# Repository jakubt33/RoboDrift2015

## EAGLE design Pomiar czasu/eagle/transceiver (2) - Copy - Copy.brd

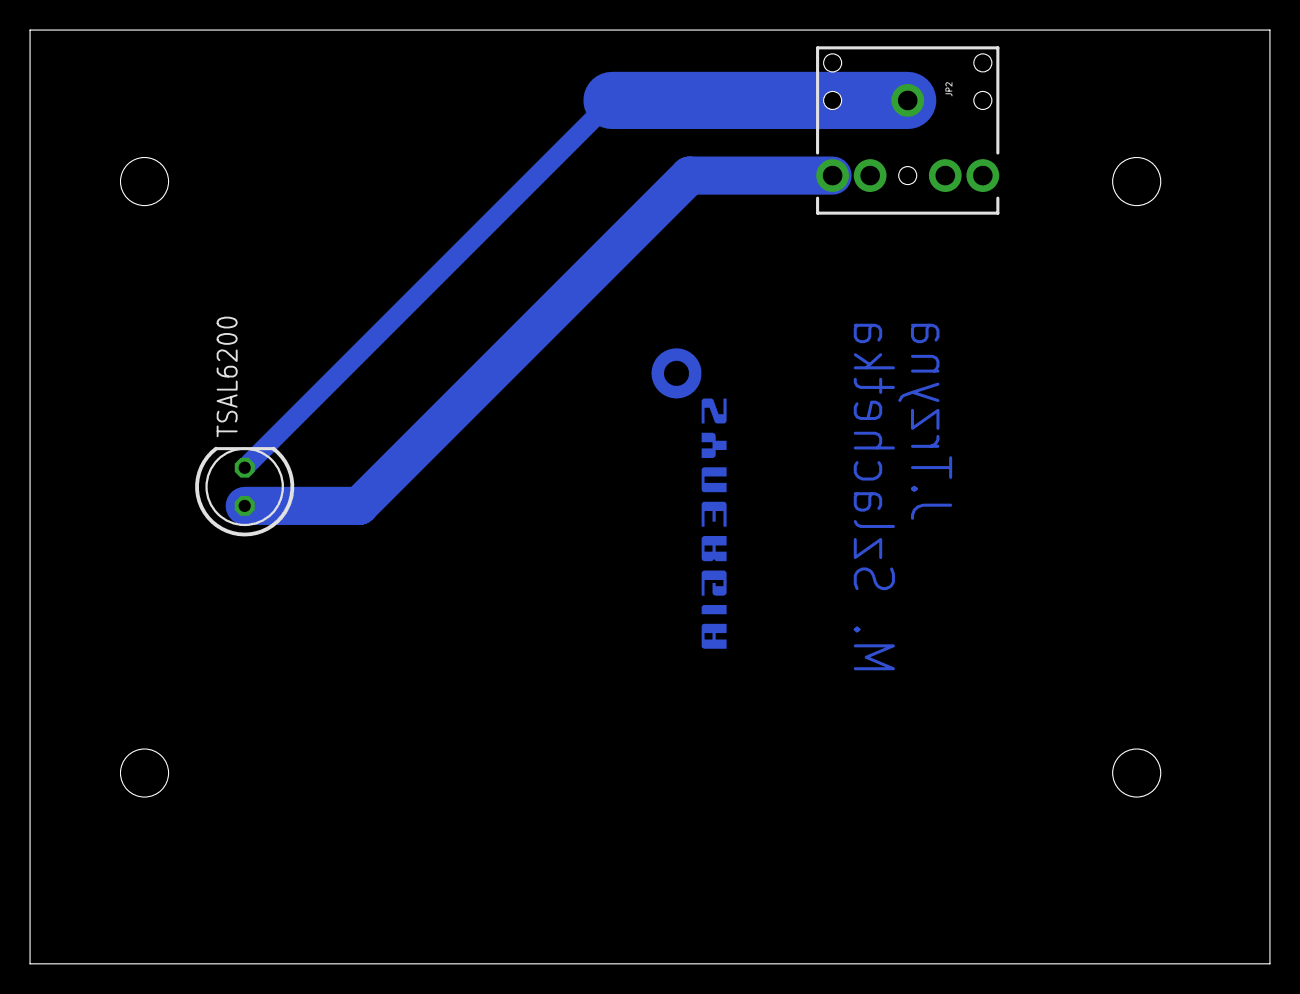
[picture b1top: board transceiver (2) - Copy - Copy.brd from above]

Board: 2 copper layers, 82.5 x 62.2 mm, 3 parts (1 on the bottom side), 2 nets.

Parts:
E$2: SYNERGIA_20MM
JP2: AUDIO-JACK
TSAL6200: LED5MM

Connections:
unnamed: JP2.TIP, TSAL6200.A
unnamed: JP2.SLEEVE, TSAL6200.K

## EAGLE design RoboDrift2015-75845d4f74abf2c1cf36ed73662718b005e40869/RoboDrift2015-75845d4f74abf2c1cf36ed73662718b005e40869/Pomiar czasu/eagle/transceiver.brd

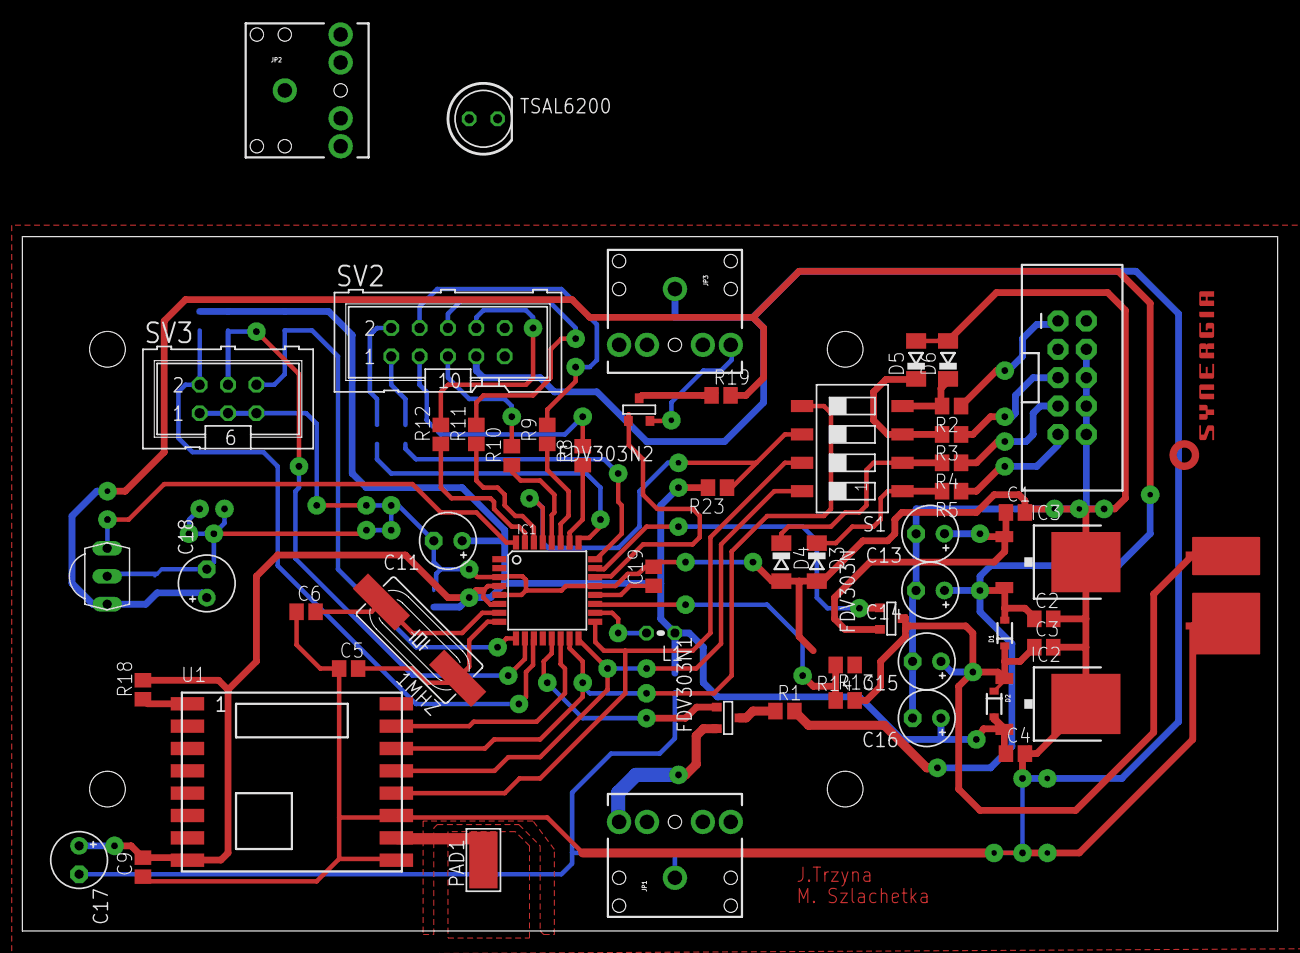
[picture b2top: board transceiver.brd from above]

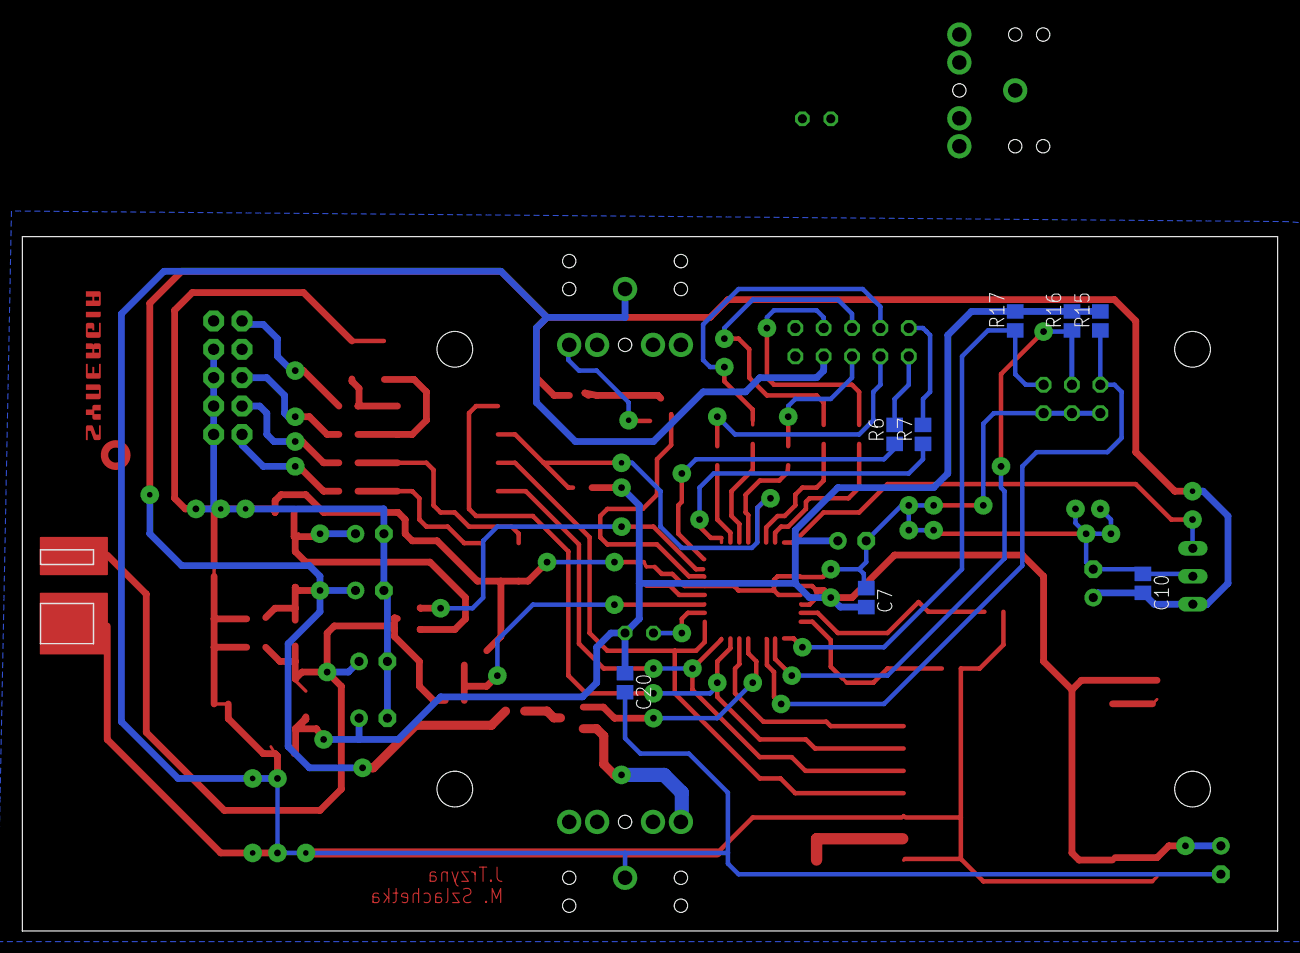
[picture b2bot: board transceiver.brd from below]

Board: 2 copper layers, 112.4 x 62.2 mm, 65 parts (8 on the bottom side), 52 nets.

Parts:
1MHZ: HC49UP
C1, C2, C3, C4, C5, C6, C7, C9, C10, C19, C20: C0805
C11, C13, C14, C15, C16, C17, C18: E2,5-5
D1, D2: BAS16HT1G; SOD-323
D3, D4, D5, D6: SOD80C
FDV303N, FDV303N1, FDV303N2: SOT-23
IC1: MEGA8-AI; TQFP32-08
IC2: LF33; TO252
IC3: LF50; TO252
JP1, JP2, JP3: AUDIO-JACK
L1: 0204V
PAD1: WIREPADSMD5-2,5; 5-2,5
R1: 36,5R; R0805
R2, R3, R4, R5, R19: R0805
R6, R7, R8, R9, R10, R12: 1.2k; R0805
R11: 1,2k; R0805
R13, R15, R16, R17, R18: 10k; R0805
R14: 3,6k; R0805
R23: 1k; R0805
S1: SWS004; SMS-004
SV2: ML10
SV3: ML6
TSAL6200: LED5MM
TSOP: TSOP4836; TSOP18XX
U1: RFM69HW; RFM69W-XXXS2
U$1: DEANS.MALE; DEANSM
U$2: AVR_SPI_PROG2PTH2; 2X5-SHROUDED
U$3: SYNERGIA_16MM

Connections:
5V_ENABLE: FDV303N.3, IC1.23
$1S1: C1.2, C2.2, C3.2, C4.2, C5.1, C6.1, C7.1, C9.1, C10.1, C11.-, C13.-, C14.-, C15.-, C16.-, C17.-, C18.-, C19.2, C20.2, D3.A, D4.A, D5.A, D6.A, IC1.3, IC1.5, IC1.21, IC2.3, IC3.3, JP1.SLEEVE, JP3.SLEEVE, R14.1, SV2.7, SV3.1, SV3.3, SV3.5, TSOP.GND, U1.9, U1.11, U$1.P$NEG, U$2.4, U$2.6, U$2.8, U$2.10
+3V3: C4.1, C7.2, C9.2, C11.+, C16.+, C17.+, C20.1, D2.2, IC1.4, IC1.6, IC2.2, L1.1, R15.2, R16.2, R17.2, R18.2, R23.2, U1.8
+5V: C2.1, C10.2, C14.+, C18.+, D1.2, IC3.2, R1.2, R19.2, TSOP.VCC
ADC: IC1.19, R13.1, R14.2
LED1: IC1.24, R6.1
LED2: IC1.25, R7.1
LED3: IC1.26, R8.1
LED4: IC1.27, R9.1
LED5: IC1.28, R10.1
LED_BATT_GR: IC1.30, R11.1
LED_BATT_RED: IC1.31, R12.1
LED_STRIPE: FDV303N2.3, IC1.22
MISO: IC1.16, S1.8, U1.13
MOSI: IC1.15, S1.5, U1.14
unnamed: C1.1, C13.+, FDV303N.2, IC3.1
unnamed: IC1.18, L1.2
unnamed: JP2.RING, TSAL6200.A
unnamed: R2.1, U$2.1
unnamed: R3.1, U$2.5
unnamed: R4.1, U$2.7
unnamed: R5.1, U$2.9
unnamed: FDV303N1.1, R1.1
unnamed: R6.2, SV2.1
unnamed: R7.2, SV2.2
unnamed: R8.2, SV2.3
unnamed: R9.2, SV2.4
unnamed: R10.2, SV2.5
unnamed: 1MHZ.2, C6.2, IC1.7
unnamed: 1MHZ.1, C5.2, IC1.8
unnamed: R11.2, SV2.6
unnamed: R12.2, SV2.8
unnamed: R18.1, U1.1
unnamed: JP2.SLEEVE, TSAL6200.K
unnamed: FDV303N1.2, JP1.RING
unnamed: FDV303N2.2, JP3.RING
unnamed: FDV303N2.1, R19.1
unnamed: C19.1, IC1.20
unnamed: C3.1, C15.+, D1.1, D2.1, FDV303N.1, IC2.1, R13.2, U$1.P$POS
unnamed: PAD1.1, U1.10
unnamed: D6.C, R2.2, S1.4
unnamed: D5.C, R3.2, S1.3
unnamed: D4.C, R4.2, S1.2
unnamed: D3.C, R5.2, S1.1
RESET: IC1.29, R23.1, S1.6
SCK: IC1.17, S1.7, U1.12
SS: IC1.14, U1.15
SWITCH_DOWN: IC1.11, R15.1, SV3.2
SWITCH_OK: IC1.10, R16.1, SV3.4
SWITCH_UP: IC1.9, R17.1, SV3.6
TSAL_ENABLE: FDV303N1.3, IC1.13
TSOP_OUT: IC1.32, TSOP.OUT

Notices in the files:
parts and their libraries:
SparkFun-Connectors: Licensing: Creative Commons ShareAlike 4.0 International - https://creativecommons.org/licenses/by-sa/4.0
SparkFun: Licensing: CC v3.0 Share-Alike You are welcome to use this library for commercial purposes.
